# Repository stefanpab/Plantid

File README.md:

# Welcome to Plantid

Plantid is an automatic watering system which works according the micro drip principle. The water will be pumped out of a watertank through a 3,7V pump.
With the help of a PVC-pipe the water will be transported to the water sprinklers - which are in the soil next to the plants. The amount of water 
coming out of the sprinkler can be adjusted by turning the head. In addition there is a web application which monitors moisture level, temperature,
the state of the pump and the current watering time. The standard watering time is 10 seconds but can always be changed manually by the user in the
web application. The watering system will start watering if the moisture value drops under 25% and will only water once a day to avoid overwatering 
the plant. In addition you can press the "EN" button to water manually. It will be watered as long as you press the button.

## Content of the folders in this repo
The folders containing following information:
* _3D Case:_ all stl versions of the case for the pcb
* _Datasheets:_ all needed datasheeds for the project
* _Documentation:_ user manuals and documenation of plantid
* _Footprints:_ additional footprints needed for kicad 7.0
* _Kicad:_ schematics and PCB layout from Kicad 7.0
* _Software:_ arduino code and web application code
* _img:_ pictures of the project

## How to use Plantid
### Arduino IDE
To use plantid you have to first download the latest version of Arduino 1. !Important! You can't use the Arduino 2.0 application because the file 
upload manager you need for the project is not supported yet. You can Download it here: https://www.arduino.cc/en/software

### Arduino IDE additional managers
In addtion you need to download the file upload manager for esp32. 
1) Download ESP32FS-1.1 zip package: https://github.com/me-no-dev/arduino-esp32fs-plugin/releases/
2) You need to know your sketchbook location from your Arduino IDE. To find that, open the Arduino IDE and go to "File->Preferences"

3) Go to the sketchbook location in your explorer and create a folder namened "tools"

4) Unzip the downloaded package and paste it into the tools folder
5) Restart the Arduino IDE
6) Now you will find under "Tools" the "ESP32 Sketch Data Upload" button

### Arduino IDE additional libraries
To make the project work you need to install some additional librarys. To install them click on Sketch->Include Library->Manage Libraries
Search for "ESP32Time" and press on install for following:

You will need two additional libraries which are not in the Library Manager. To install them go to File->Preferences
Click on following button:

Paste then the following line into it and press ok. With that line you will install the the AsyncTCP and the AsynchWebServer which are 
necassary to build the asynchrouns webserver.
"https://github.com/me-no-dev/ESPAsyncWebServer; https://github.com/me-no-dev/AsyncTCP"

### Code adjustments
To edit the arduino code, you have to open the /Software/plantid_sw/plantid_sw.ino file. 
You can make several changes in this file which best fits for your usecase. At line 48 and 49 you have to replace those wifi credentials with your 
home wife name and password. In addition you can open /Software/plantid_sw/data/index.html to change the web application. You can change the CSS, or 
removing for example the pump state to be seen on the web gui. After finishing the editing of those files, go back to the Arduino Software.
Plug in a micro USB cable into the ESP32 and into your computer. Now go to "tools" and press the "ESP32 Sketch Data Upload" button. In most cases you 
now have to press the boot button for two seconds. After you get the message "Done uploading" in the arduino console, the index.html is 
successfully be uploaded. Now you have to upload the code. Click on tools and apply following settings:

Most important are Port and Board. Select "ESP32 Dev Module" as board and for the port the correct one where your ESP32 is plugged in. After selecting
the correct settings press the upload button (button in the red rectangle). In most cases it can be necassary to press the boot button again to 
successfully upload the code. After uploading the Code you can plug out the micro USB cable and screw the battery wires into the screw clamp.

### Web GUI
Now after uploading everything you can open the web gui by entering "plantid.local" in any internet explorer. You will now be able to see the current 
values of the watering system. In addition you can manually change the watering time by entering your needed time in seconds and confirming that by
pressing the "Change value" button.

### Hardware
Fill the tank with water but fill it no higher than the plant pot to avoid that the water won't stop floating after watering. Plant your plants into the 
pot and place the moisture sensor in the pot. For the best results from the sensor, bury the sensor as deep as possible under the plants. Scew the PCB into
the 3D case and connect the pump, sensor and battery to the pcb. Close the PCB and plug the pipes into the pump and the water tank.

## Documentation
In the documentation folder you can find the ibom file. This file shows you an interactive instruction how to solder the pcb with which components. In 
addition you have the components list as an csv file to know the order number of the required parts. Also you can find the circuit diagram, so you dont have 
to download KiCad to have a look at it. Last but not least you will also find the block diagram in there.

# Support
If you run into any problems or have any questions regarding the project, feel free to message me under my email: sa21b004@technikum-wien.at

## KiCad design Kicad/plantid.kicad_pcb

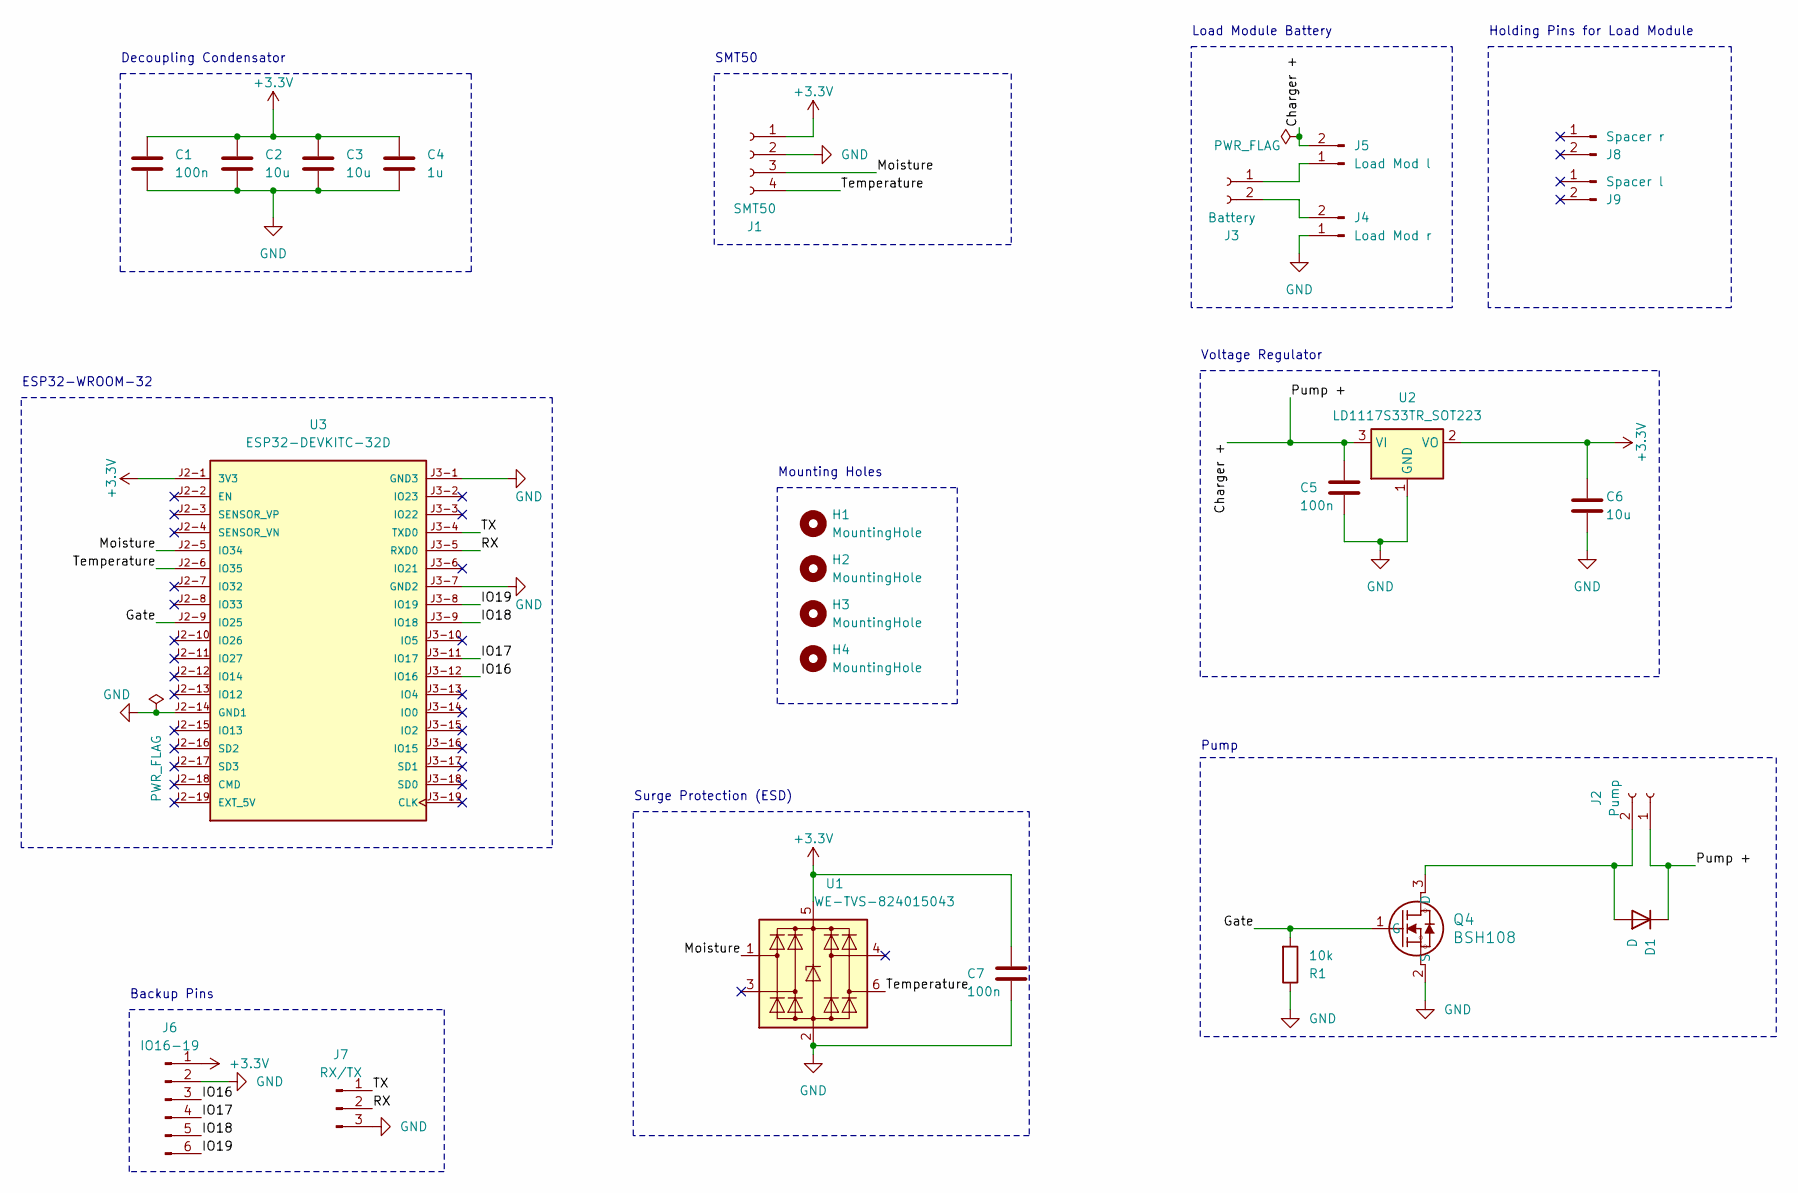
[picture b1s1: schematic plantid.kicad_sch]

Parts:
C1, C5, C7: 100n; C_0603_1608Metric_Pad1.08x0.95mm_HandSolder; Digikey 1276-1000-1-ND
C2, C3, C6: 10u; C_0603_1608Metric_Pad1.08x0.95mm_HandSolder; Digikey 1276-1038-1-ND
C4: 1u; C_0603_1608Metric_Pad1.08x0.95mm_HandSolder; Digikey 1276-1038-1-ND
D1: D; D_DO-41_SOD81_P10.16mm_Horizontal
H1, H2, H3, H4: MountingHole; MountingHole_2.2mm_M2
J1: SMT50; CONN_OSTVN04A150_OST; Digikey ED10563-ND
J2: Pump; CONN_OSTVN02A150_OST; Digikey ED10561-ND
J3: Battery; CONN_OSTVN02A150_OST; Digikey ED10561-ND
J4: Load Mod r; PinHeader_1x02_P2.54mm_Vertical
J5: Load Mod l; PinHeader_1x02_P2.54mm_Vertical
J6: IO16-19; PinHeader_1x06_P2.54mm_Vertical
J7: RX/TX; PinHeader_1x03_P2.54mm_Vertical
J8: Spacer r; PinHeader_1x02_P2.54mm_Vertical
J9: Spacer l; PinHeader_1x02_P2.54mm_Vertical
Q4: BSH108; SOT23_NXP; Digikey 1727-4925-2-ND
R1: 10k; R_0603_1608Metric_Pad0.98x0.95mm_HandSolder; Digikey RMCF0603FT10K0CT-ND
U1: WE-TVS-824015043; SOT-23-6_Handsoldering; Digikey D1213A-04SO-7DITR-ND
U2: LD1117S33TR_SOT223; TO255P1020X450X1968-3; Digikey 497-1491-5-ND
U3: ESP32-DEVKITC-32D; MODULE_ESP32-DEVKITC-32D; PARTREV V4; Digikey 1965-1000-ND

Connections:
+3.3V: C1.2, C2.2, C3.2, C4.2, C6.1, C7.1, J1.1, J6.1, U1.5 (VBUS), U2.2 (VO), U3.J2-1 (3V3)
/Charger +: C5.1, D1.1 (K), J2.1, J5.2, U2.3 (VI)
/Gate: Q4.1 (G), R1.2, U3.J2-9 (IO25)
/IO16: J6.3, U3.J3-12 (IO16)
/IO17: J6.4, U3.J3-11 (IO17)
/IO18: J6.5, U3.J3-9 (IO18)
/IO19: J6.6, U3.J3-8 (IO19)
/Moisture: J1.3, U1.1 (I/O1), U3.J2-5 (IO34)
/RX: J7.2, U3.J3-5 (RXD0)
/TX: J7.1, U3.J3-4 (TXD0)
/Temperature: J1.4, U1.6 (I/O4), U3.J2-6 (IO35)
GND: C1.1, C2.1, C3.1, C4.1, C5.2, C6.2, C7.2, J1.2, J4.1, J6.2, J7.3, Q4.2 (S), R1.1, U1.2 (GND), U2.1 (GND), U3.J2-14 (GND1), U3.J3-1 (GND3), U3.J3-7 (GND2)
unnamed: D1.2 (A), J2.2, Q4.3 (D)
unnamed: J3.1, J5.1
unnamed: J3.2, J4.2

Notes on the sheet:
SMT50
Backup Pins
ESP32-WROOM-32
Surge Protection (ESD)
Load Module Battery
Mounting Holes
Voltage Regulator
Decoupling Condensator
Holding Pins for Load Module
Pump

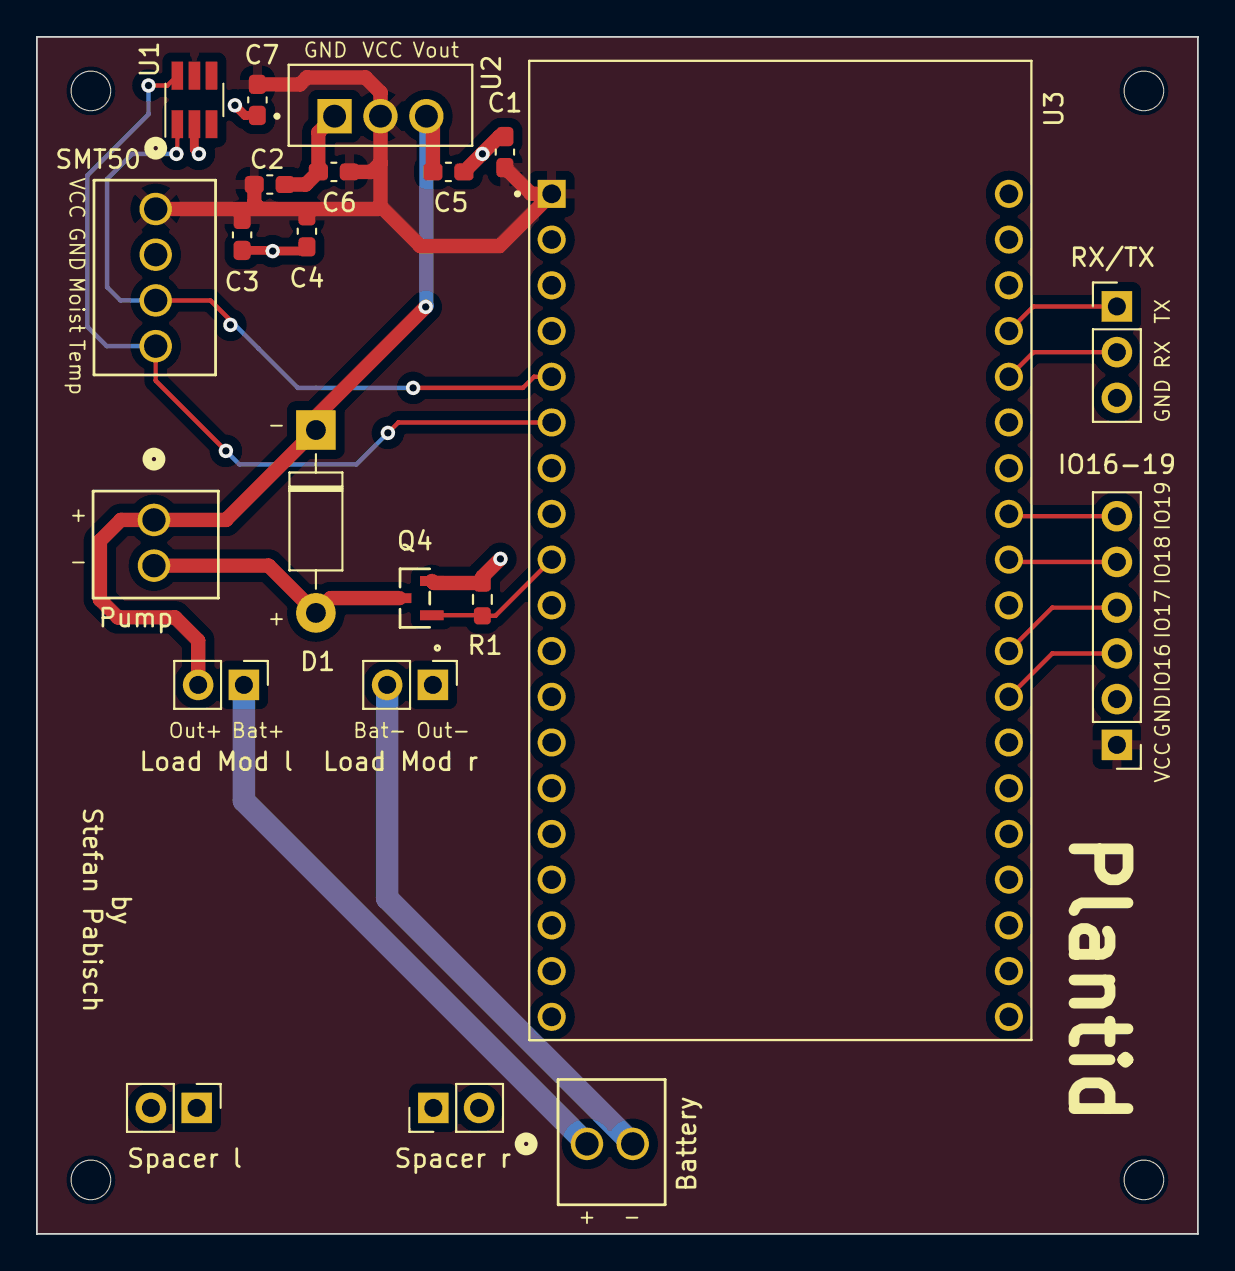
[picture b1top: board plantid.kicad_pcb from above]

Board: 2 copper layers, 64.5 x 66.5 mm, 26 parts (0 on the bottom side), 15 nets.

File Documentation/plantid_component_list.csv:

"Reference","Value","Footprint","Datasheet","Digikey","Reichelt","Menge"
"C1, C5, C7","100n","Capacitor_SMD:C_0603_1608Metric_Pad1.08x0.95mm_HandSolder","~","1276-1000-1-ND","","3"
"C2, C3, C6","10u","Capacitor_SMD:C_0603_1608Metric_Pad1.08x0.95mm_HandSolder","~","1276-1038-1-ND","","3"
"C4","1u","Capacitor_SMD:C_0603_1608Metric_Pad1.08x0.95mm_HandSolder","~","1276-1038-1-ND","","1"
"D1","D","Diode_THT:D_DO-41_SOD81_P10.16mm_Horizontal","~","","1N 4001","1"
"H1-H4","MountingHole","MountingHole:MountingHole_2.2mm_M2","~","","","4"
"J1","SMT50","1x04 Connector:CONN_OSTVN04A150_OST","~","ED10563-ND","","1"
"J2","Pump","1x02 Connector:CONN_OSTVN02A150_OST","~","ED10561-ND","","1"
"J3","Battery","1x02 Connector:CONN_OSTVN02A150_OST","~","ED10561-ND","","1"
"J4","Load Mod r","Connector_PinHeader_2.54mm:PinHeader_1x02_P2.54mm_Vertical","~","","MPE 087-1-002","1"
"J5","Load Mod l","Connector_PinHeader_2.54mm:PinHeader_1x02_P2.54mm_Vertical","~","","MPE 087-1-002","1"
"J6","IO16-19","Connector_PinHeader_2.54mm:PinHeader_1x06_P2.54mm_Vertical","~","","MPE 087-1-006","1"
"J7","RX/TX","Connector_PinHeader_2.54mm:PinHeader_1x03_P2.54mm_Vertical","~","","MPE 087-1-003","1"
"J8","Spacer r","Connector_PinHeader_2.54mm:PinHeader_1x02_P2.54mm_Vertical","~","","MPE 087-1-002","1"
"J9","Spacer l","Connector_PinHeader_2.54mm:PinHeader_1x02_P2.54mm_Vertical","~","","MPE 087-1-002","1"
"Q4","BSH108","BSH108:SOT23_NXP","BSH108","1727-4925-2-ND","","1"
"R1","10k","Resistor_SMD:R_0603_1608Metric_Pad0.98x0.95mm_HandSolder","~","RMCF0603FT10K0CT-ND","","1"
"U1","WE-TVS-824015043","Package_TO_SOT_SMD:SOT-23-6_Handsoldering","https://www.we-online.com/components/products/datasheet/8240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","D1213A-04SO-7DITR-ND","","1"
"U2","LD1117S33TR_SOT223","LD1117V33:TO255P1020X450X1968-3","http://www.st.com/st-web-ui/static/active/en/resource/techni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","497-1491-5-ND","","1"
"U3","ESP32-DEVKITC-32D","ESP32-DEVKITC-32D:MODULE_ESP32-DEVKITC-32D","","1965-1000-ND","","1"

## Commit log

2023-11-13 removed files
2023-11-15 changed to english
2023-11-17 fixed displaying temp and moist
2023-11-20 updated ino and html
2023-11-24 deep sleep added
2023-11-24 added 3d files
2023-11-27 added RTC clock
2023-11-27 added new versions of the 3d model
2023-11-28 added function to change watering time by user input
2023-11-29 added sliced files
2023-12-08 added testfiles and some little fixes
2023-12-09 made some changes
2023-12-09 added wateringtime displaying from preferences
2023-12-09 minor changes
2023-12-11 changed fail functions
2023-12-11 changed some minor changes
2023-12-26 updated preferneces function to set watering time
2023-12-26 fixed an error with int
2024-01-07 added external wifi credentials
2024-01-15 updated some changes
    set milliseconds to seconds in html.
    added mdns
    added wifimanager
    added manuell watering per gpio0
2024-01-15 added manuell button to water
2024-01-17 added docu
2024-01-21 final changes
2024-01-25 added img
2024-01-25 added docu files and commands in arduino file
2024-01-27 added file
